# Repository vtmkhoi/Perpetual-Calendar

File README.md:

# Perpetual-Calendar
Create a perpetual calendar using microcontroller AVR8bits, displayed on 7-segments via IC Max7219

# Have done
 - Interface Atmega32 with MAX7219
 - Interface Atmega32 with DS1307	
 - Algorithm for perpetual calendar
 - Adjust hour; minutes; day; month
 - Design PCB layout
 - Fullfilled displayed with mentor's requirements

# Haven't done
 - Blynk 7segments LED in Adjust's mode
<<<<<<< HEAD
 - revenge noise from button and SPI protocal
=======
 - Decrease noise from button and SPI protocal
>>>>>>> 75059a2ca367e3f0e033ad3231786ee3f7a5212f

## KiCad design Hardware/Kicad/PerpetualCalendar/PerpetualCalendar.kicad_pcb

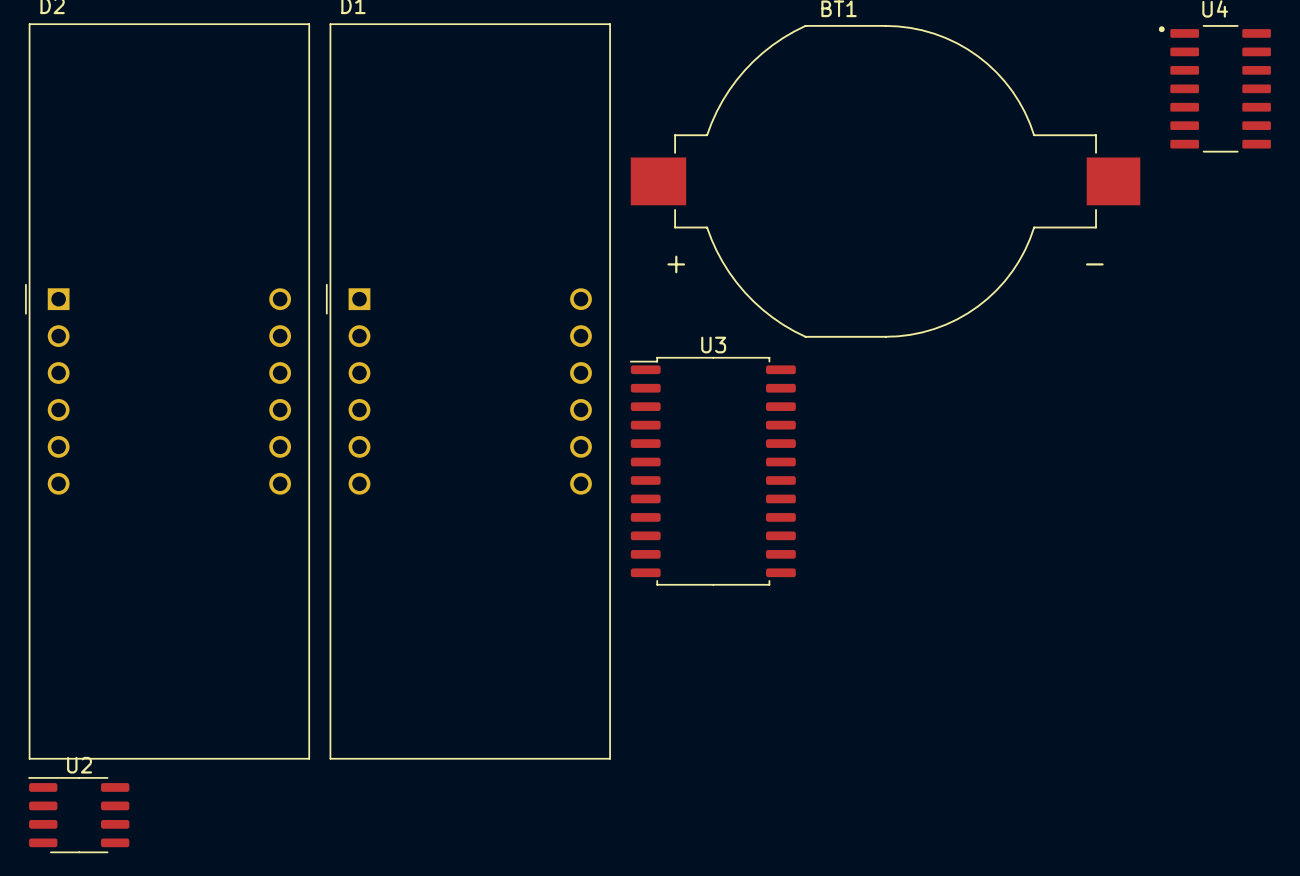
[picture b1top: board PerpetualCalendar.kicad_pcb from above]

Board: 2 copper layers, 6 parts (0 on the bottom side), 18 nets, no tracks yet.

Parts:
BT1: Battery_Cell; BAT_BC2032-F1
D1: ABOVE; CA56-12CGKWA
D2: BELOW; CA56-12CGKWA
U2: DS1307Z+; SOIC-8_3.9x4.9mm_P1.27mm
U3: MAX7221; SOIC-24W_7.5x15.4mm_P1.27mm
U4: CD40106; SOIC127P600X175-14N

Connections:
/DIG0: D1.12 (CC1), U3.2 (DIG_0)
/DIG1: D1.9 (CC2), U3.11 (DIG_1)
/DIG2: D1.8 (CC3), U3.6 (DIG_2)
/DIG3: D1.6 (CC4), U3.7 (DIG_3)
/DIG4: D2.12 (CC1), U3.3 (DIG_4)
/DIG5: D2.9 (CC2), U3.10 (DIG_5)
/DIG6: D2.8 (CC3), U3.5 (DIG_6)
/DIG7: D2.6 (CC4), U3.8 (DIG_7)
/SEG_A: D1.11 (a), D2.11 (a)
/SEG_B: D1.7 (b), D2.7 (b)
/SEG_C: D1.4 (c), D2.4 (c)
/SEG_D: D1.2 (d), D2.2 (d)
/SEG_DP: D1.3 (DPX), D2.3 (DPX)
/SEG_E: D1.1 (e), D2.1 (e)
/SEG_F: D1.10 (f), D2.10 (f)
/SEG_G: D1.5 (g), D2.5 (g)
GND: U2.4 (GND), U4.7 (VSS)
unnamed: U3.4 (GND), U3.9 (GND)

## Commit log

2021-12-01 add Test file
2021-12-01 add 'Test_DS1307'
2021-12-06 add calendar_01
2021-12-06 add lichnew
2021-12-09 add file 3 buttons
2021-12-14 add PCB layout
2021-12-16 missed: 7seg, micro-usb
2021-12-16 upd Readme, PCB-design
2021-12-17 add final version
2021-12-17 update schematic
2021-12-20 add Sche
2021-12-20 edit README
2021-12-22 add components list
2021-12-24 edit sche
2021-12-25 add PCB design
2021-12-27 add PCB
2022-01-05 add README
2022-01-05 upd README
2022-01-08 PCB ver01
2022-01-20 Last version
2022-01-20 Add Test IO
2022-01-20 Video clip
2022-09-02 Update gitignore
2022-09-02 no message
2022-09-10 Update gitignore, Update schematic and some component's footprint
